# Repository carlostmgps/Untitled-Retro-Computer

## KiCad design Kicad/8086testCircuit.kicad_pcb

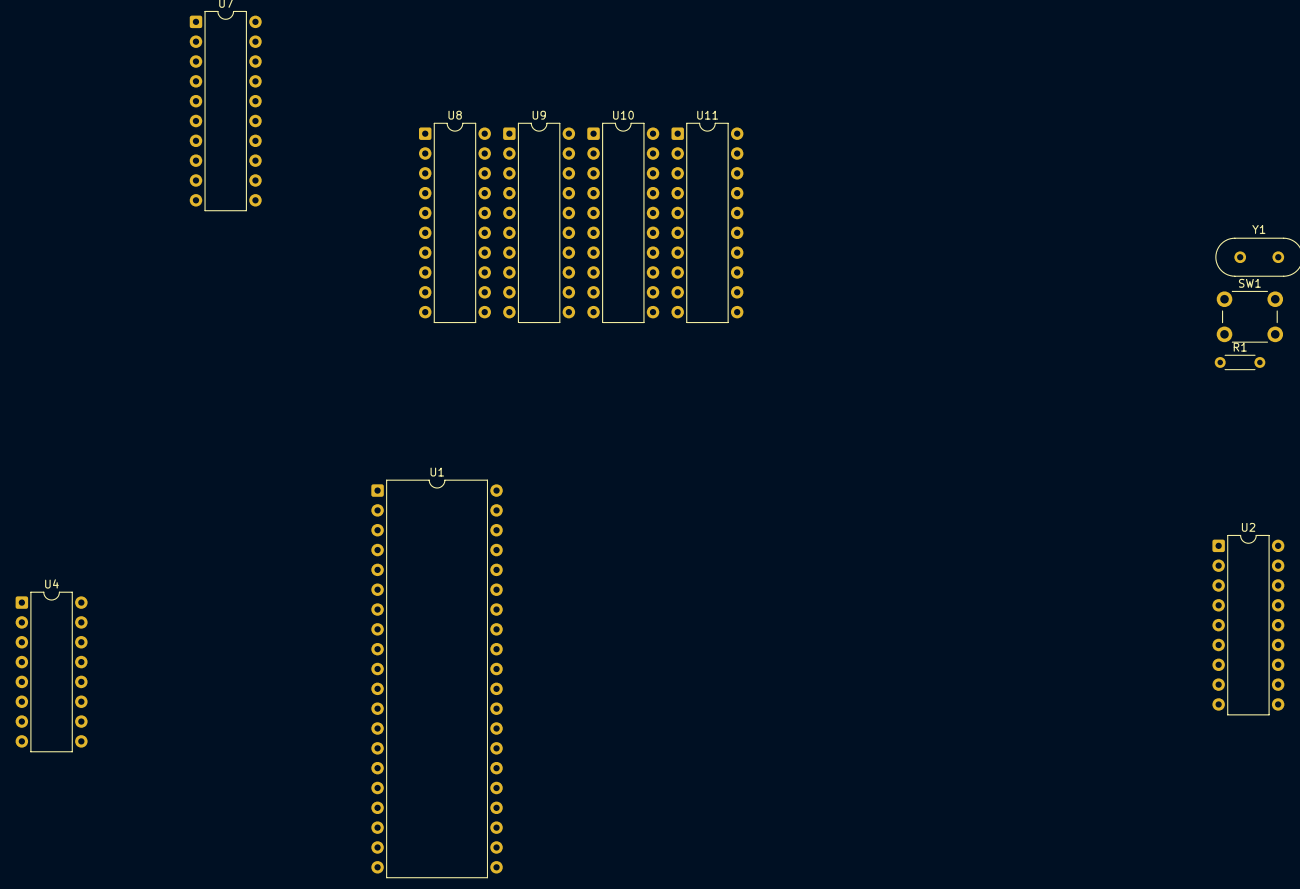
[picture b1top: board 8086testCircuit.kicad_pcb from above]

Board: 2 copper layers, 11 parts (0 on the bottom side), 34 nets, no tracks yet.

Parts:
R1: 10k; R_Axial_DIN0204_L3.6mm_D1.6mm_P5.08mm_Horizontal
SW1: RST; SW_PUSH_6mm
U1: 8086-1_Min_Mode; DIP-40_W15.24mm
U2: 8284; DIP-18_W7.62mm
U4: 74HCT138; DIP-16_W7.62mm
U7, U9, U10: 74HCT573; DIP-20_W7.62mm
U8, U11: 74HCT245; DIP-20_W7.62mm
Y1: Crystal 30MHz; Crystal_HC49-U_Vertical

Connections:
/CPU/5V: U1.33 (MN/~MX), U1.40 (VCC), U4.6 (E2), U4.16 (VCC), U7.20 (VCC), U8.20 (VCC), U9.20 (VCC), U10.20 (VCC), U11.20 (VCC)
/CPU/!BHE: U1.34 (~BHE/S7), U10.6 (D4), U10.15 (Q4)
/CPU/!DEN: U1.26 (~DEN), U8.19 (CE), U11.19 (CE)
/CPU/AD0: U1.16 (AD0), U7.2 (D0), U8.2 (A0)
/CPU/AD1: U1.15 (AD1), U7.3 (D1), U8.3 (A1)
/CPU/AD2: U1.14 (AD2), U7.4 (D2), U8.4 (A2)
/CPU/AD3: U1.13 (AD3), U7.5 (D3), U8.5 (A3)
/CPU/AD4: U1.12 (AD4), U7.6 (D4), U8.6 (A4)
/CPU/AD5: U1.11 (AD5), U7.7 (D5), U8.7 (A5)
/CPU/AD6: U1.10 (AD6), U7.8 (D6), U8.8 (A6)
/CPU/AD7: U1.9 (AD7), U7.9 (D7), U8.9 (A7)
/CPU/AD8: U1.8 (AD8), U9.2 (D0), U11.2 (A0)
/CPU/AD9: U1.7 (AD9), U9.3 (D1), U11.3 (A1)
/CPU/AD10: U1.6 (AD10), U9.4 (D2), U11.4 (A2)
/CPU/AD11: U1.5 (AD11), U9.5 (D3), U11.5 (A3)
/CPU/AD12: U1.4 (AD12), U9.6 (D4), U11.6 (A4)
/CPU/AD13: U1.3 (AD13), U9.7 (D5), U11.7 (A5)
/CPU/AD14: U1.2 (AD14), U9.8 (D6), U11.8 (A6)
/CPU/AD15: U1.39 (AD15), U9.9 (D7), U11.9 (A7)
/CPU/AD16: U1.38 (A16/S3), U10.2 (D0)
/CPU/AD17: U1.37 (A17/S4), U10.3 (D1)
/CPU/AD18: U1.36 (A18/S5), U10.4 (D2)
/CPU/AD19: U1.35 (A19/S6), U10.5 (D3)
/CPU/ALE: U1.25 (ALE), U7.11 (Load), U9.11 (Load), U10.11 (Load)
/CPU/DT/!R: U1.27 (DT/~R), U8.1 (A->B), U11.1 (A->B)
/CPU/GND: U1.1 (GND), U1.20 (GND), U4.4 (~E0), U4.5 (~E1), U4.8 (GND), U7.1 (OE), U7.10 (GND), U8.10 (GND), U9.1 (OE), U9.10 (GND), U10.1 (OE), U10.10 (GND), U11.10 (GND)
/Clock/!RES: R1.1, SW1.2, U2.4 (RDY1), U2.18 (VCC)
/Clock/GND: SW1.1, U2.1 (CSYNC), U2.3 (~AEN1), U2.6 (RDY2), U2.7 (~AEN2), U2.9 (GND), U2.13 (F/~C), U2.15 (~ASYNC)
unnamed: U1.28 (M/~IO), U4.3 (A2)
unnamed: U1.32 (~RD), U4.2 (A1)
unnamed: U1.29 (~WR), U4.1 (A0)
unnamed: U2.17 (X1), Y1.2
unnamed: U2.16 (X2), Y1.1
unnamed: R1.2, U2.11 (~RES)

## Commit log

2026-04-18 Add project documentation for development progress
    Document project goals, modules needed, and progress updates for day 1 and day 2 of development.
